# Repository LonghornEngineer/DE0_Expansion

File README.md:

***
###DE0_Expansion
***
**Expansion template for the Altera DE0 Development Board.**

This template fits the 2 40Pin GPIO expansion headers for the [Altera DE0 Development Board by terasIC](http://www.terasic.com.tw/cgi-bin/page/archive.pl?Language=English&No=364). 

Files are for Eagle V6.0+ 

***

***

See [here for more information](http://longhornengineer.com/category/projects/hardware/de0-expansion-template/).

***
**License Information**

This project is under the [Creative Commons Attribution-ShareAlike 4.0 International License](LICENSE.md). These files are provided with no warranty and should be used at your own risk. 

***

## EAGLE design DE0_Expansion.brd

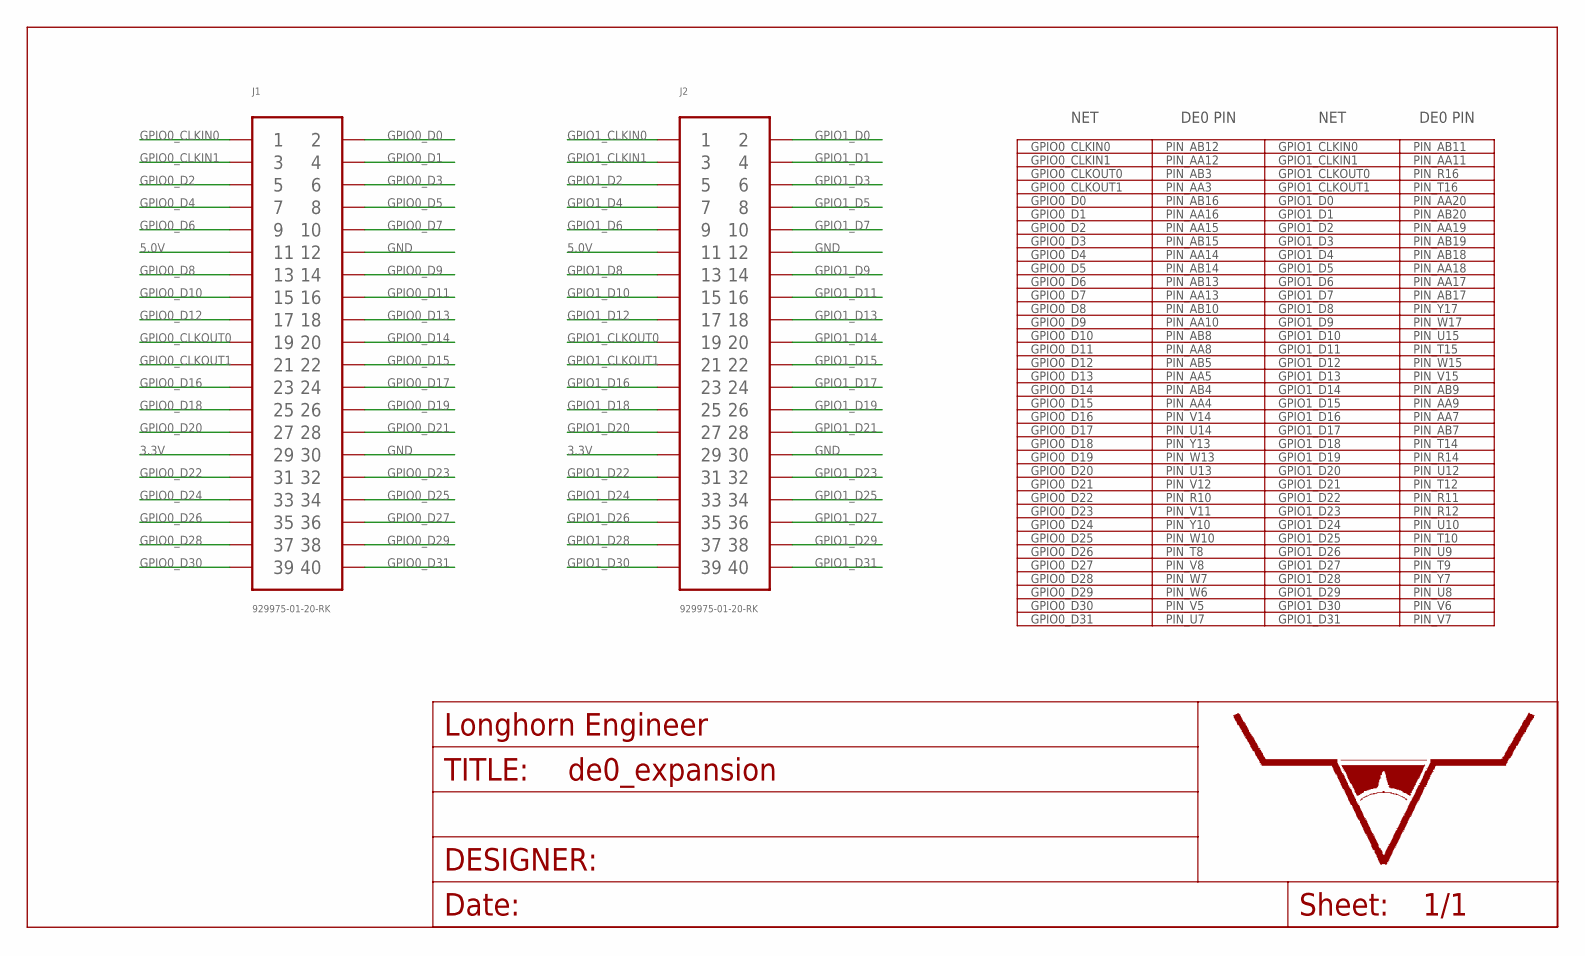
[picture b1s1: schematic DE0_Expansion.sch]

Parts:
FRAME: LHE_FRAME
J1, J2: 929975-01-20-RK; HEADER_02X20_PTH

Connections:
3.3V: J1.29, J2.29
5.0V: J1.11, J2.11
GND: J1.12, J1.30, J2.12, J2.30
GPIO0_CLKIN0: J1.1
GPIO0_CLKIN1: J1.3
GPIO0_CLKOUT0: J1.19
GPIO0_CLKOUT1: J1.21
GPIO0_D0: J1.2
GPIO0_D1: J1.4
GPIO0_D2: J1.5
GPIO0_D3: J1.6
GPIO0_D4: J1.7
GPIO0_D5: J1.8
GPIO0_D6: J1.9
GPIO0_D7: J1.10
GPIO0_D8: J1.13
GPIO0_D9: J1.14
GPIO0_D10: J1.15
GPIO0_D11: J1.16
GPIO0_D12: J1.17
GPIO0_D13: J1.18
GPIO0_D14: J1.20
GPIO0_D15: J1.22
GPIO0_D16: J1.23
GPIO0_D17: J1.24
GPIO0_D18: J1.25
GPIO0_D19: J1.26
GPIO0_D20: J1.27
GPIO0_D21: J1.28
GPIO0_D22: J1.31
GPIO0_D23: J1.32
GPIO0_D24: J1.33
GPIO0_D25: J1.34
GPIO0_D26: J1.35
GPIO0_D27: J1.36
GPIO0_D28: J1.37
GPIO0_D29: J1.38
GPIO0_D30: J1.39
GPIO0_D31: J1.40
GPIO1_CLKIN0: J2.1
GPIO1_CLKIN1: J2.3
GPIO1_CLKOUT0: J2.19
GPIO1_CLKOUT1: J2.21
GPIO1_D0: J2.2
GPIO1_D1: J2.4
GPIO1_D2: J2.5
GPIO1_D3: J2.6
GPIO1_D4: J2.7
GPIO1_D5: J2.8
GPIO1_D6: J2.9
GPIO1_D7: J2.10
GPIO1_D8: J2.13
GPIO1_D9: J2.14
GPIO1_D10: J2.15
GPIO1_D11: J2.16
GPIO1_D12: J2.17
GPIO1_D13: J2.18
GPIO1_D14: J2.20
GPIO1_D15: J2.22
GPIO1_D16: J2.23
GPIO1_D17: J2.24
GPIO1_D18: J2.25
GPIO1_D19: J2.26
GPIO1_D20: J2.27
GPIO1_D21: J2.28
GPIO1_D22: J2.31
GPIO1_D23: J2.32
GPIO1_D24: J2.33
GPIO1_D25: J2.34
GPIO1_D26: J2.35
GPIO1_D27: J2.36
GPIO1_D28: J2.37
GPIO1_D29: J2.38
GPIO1_D30: J2.39
GPIO1_D31: J2.40

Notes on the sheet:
GPIO0_CLKIN0 GPIO0_CLKIN1 GPIO0_CLKOUT0 GPIO0_CLKOUT1 GPIO0_D0 GPIO0_D1 GPIO0_D2 GPIO0_D3 GPIO0_D4 GPIO0_D5 GPIO0_D6 GPIO0_D7 GPIO0_D8 GPIO0_D9 GPIO0_D10 GPIO0_D11 GPIO0_D12 GPIO0_D13 GPIO0_D14 GPIO0_D15 GPIO0_D16 GPIO0_D17 GPIO0_D18 GPIO0_D19 GPIO0_D20 GPIO0_D21 GPIO0_D22 GPIO0_D23 GPIO0_D24 GPIO0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
GPIO1_CLKIN0 GPIO1_CLKIN1 GPIO1_CLKOUT0 GPIO1_CLKOUT1 GPIO1_D0 GPIO1_D1 GPIO1_D2 GPIO1_D3 GPIO1_D4 GPIO1_D5 GPIO1_D6 GPIO1_D7 GPIO1_D8 GPIO1_D9 GPIO1_D10 GPIO1_D11 GPIO1_D12 GPIO1_D13 GPIO1_D14 GPIO1_D15 GPIO1_D16 GPIO1_D17 GPIO1_D18 GPIO1_D19 GPIO1_D20 GPIO1_D21 GPIO1_D22 GPIO1_D23 GPIO1_D24 GPIO1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
PIN_AB12 PIN_AA12 PIN_AB3 PIN_AA3 PIN_AB16 PIN_AA16 PIN_AA15 PIN_AB15 PIN_AA14 PIN_AB14 PIN_AB13 PIN_AA13 PIN_AB10 PIN_AA10 PIN_AB8 PIN_AA8 PIN_AB5 PIN_AA5 PIN_AB4 PIN_AA4 PIN_V14 PIN_U14 PIN_Y13 PIN_W13 PIN_U13 PIN_V12 PIN_R10 PIN_V11 PIN_Y10 PIN_W10 PIN_T8 PIN_V8 PIN_W7 PIN_W6 PIN_V5 PIN_U7
PIN_AB11 PIN_AA11 PIN_R16 PIN_T16 PIN_AA20 PIN_AB20 PIN_AA19 PIN_AB19 PIN_AB18 PIN_AA18 PIN_AA17 PIN_AB17 PIN_Y17 PIN_W17 PIN_U15 PIN_T15 PIN_W15 PIN_V15 PIN_AB9 PIN_AA9 PIN_AA7 PIN_AB7 PIN_T14 PIN_R14 PIN_U12 PIN_T12 PIN_R11 PIN_R12 PIN_U10 PIN_T10 PIN_U9 PIN_T9 PIN_Y7 PIN_U8 PIN_V6 PIN_V7
NET
DE0 PIN

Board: 2 copper layers, 3 parts (0 on the bottom side), 3 nets, no tracks yet.

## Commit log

2015-01-26 Adding the Template and Images.
2015-01-26 Testing images in markdown
2015-01-26 Finishing Readme
2016-08-23 updating readme.

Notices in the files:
parts and their libraries:
PP_Aesthetics: (c) 2015 Longhorn Engineer
